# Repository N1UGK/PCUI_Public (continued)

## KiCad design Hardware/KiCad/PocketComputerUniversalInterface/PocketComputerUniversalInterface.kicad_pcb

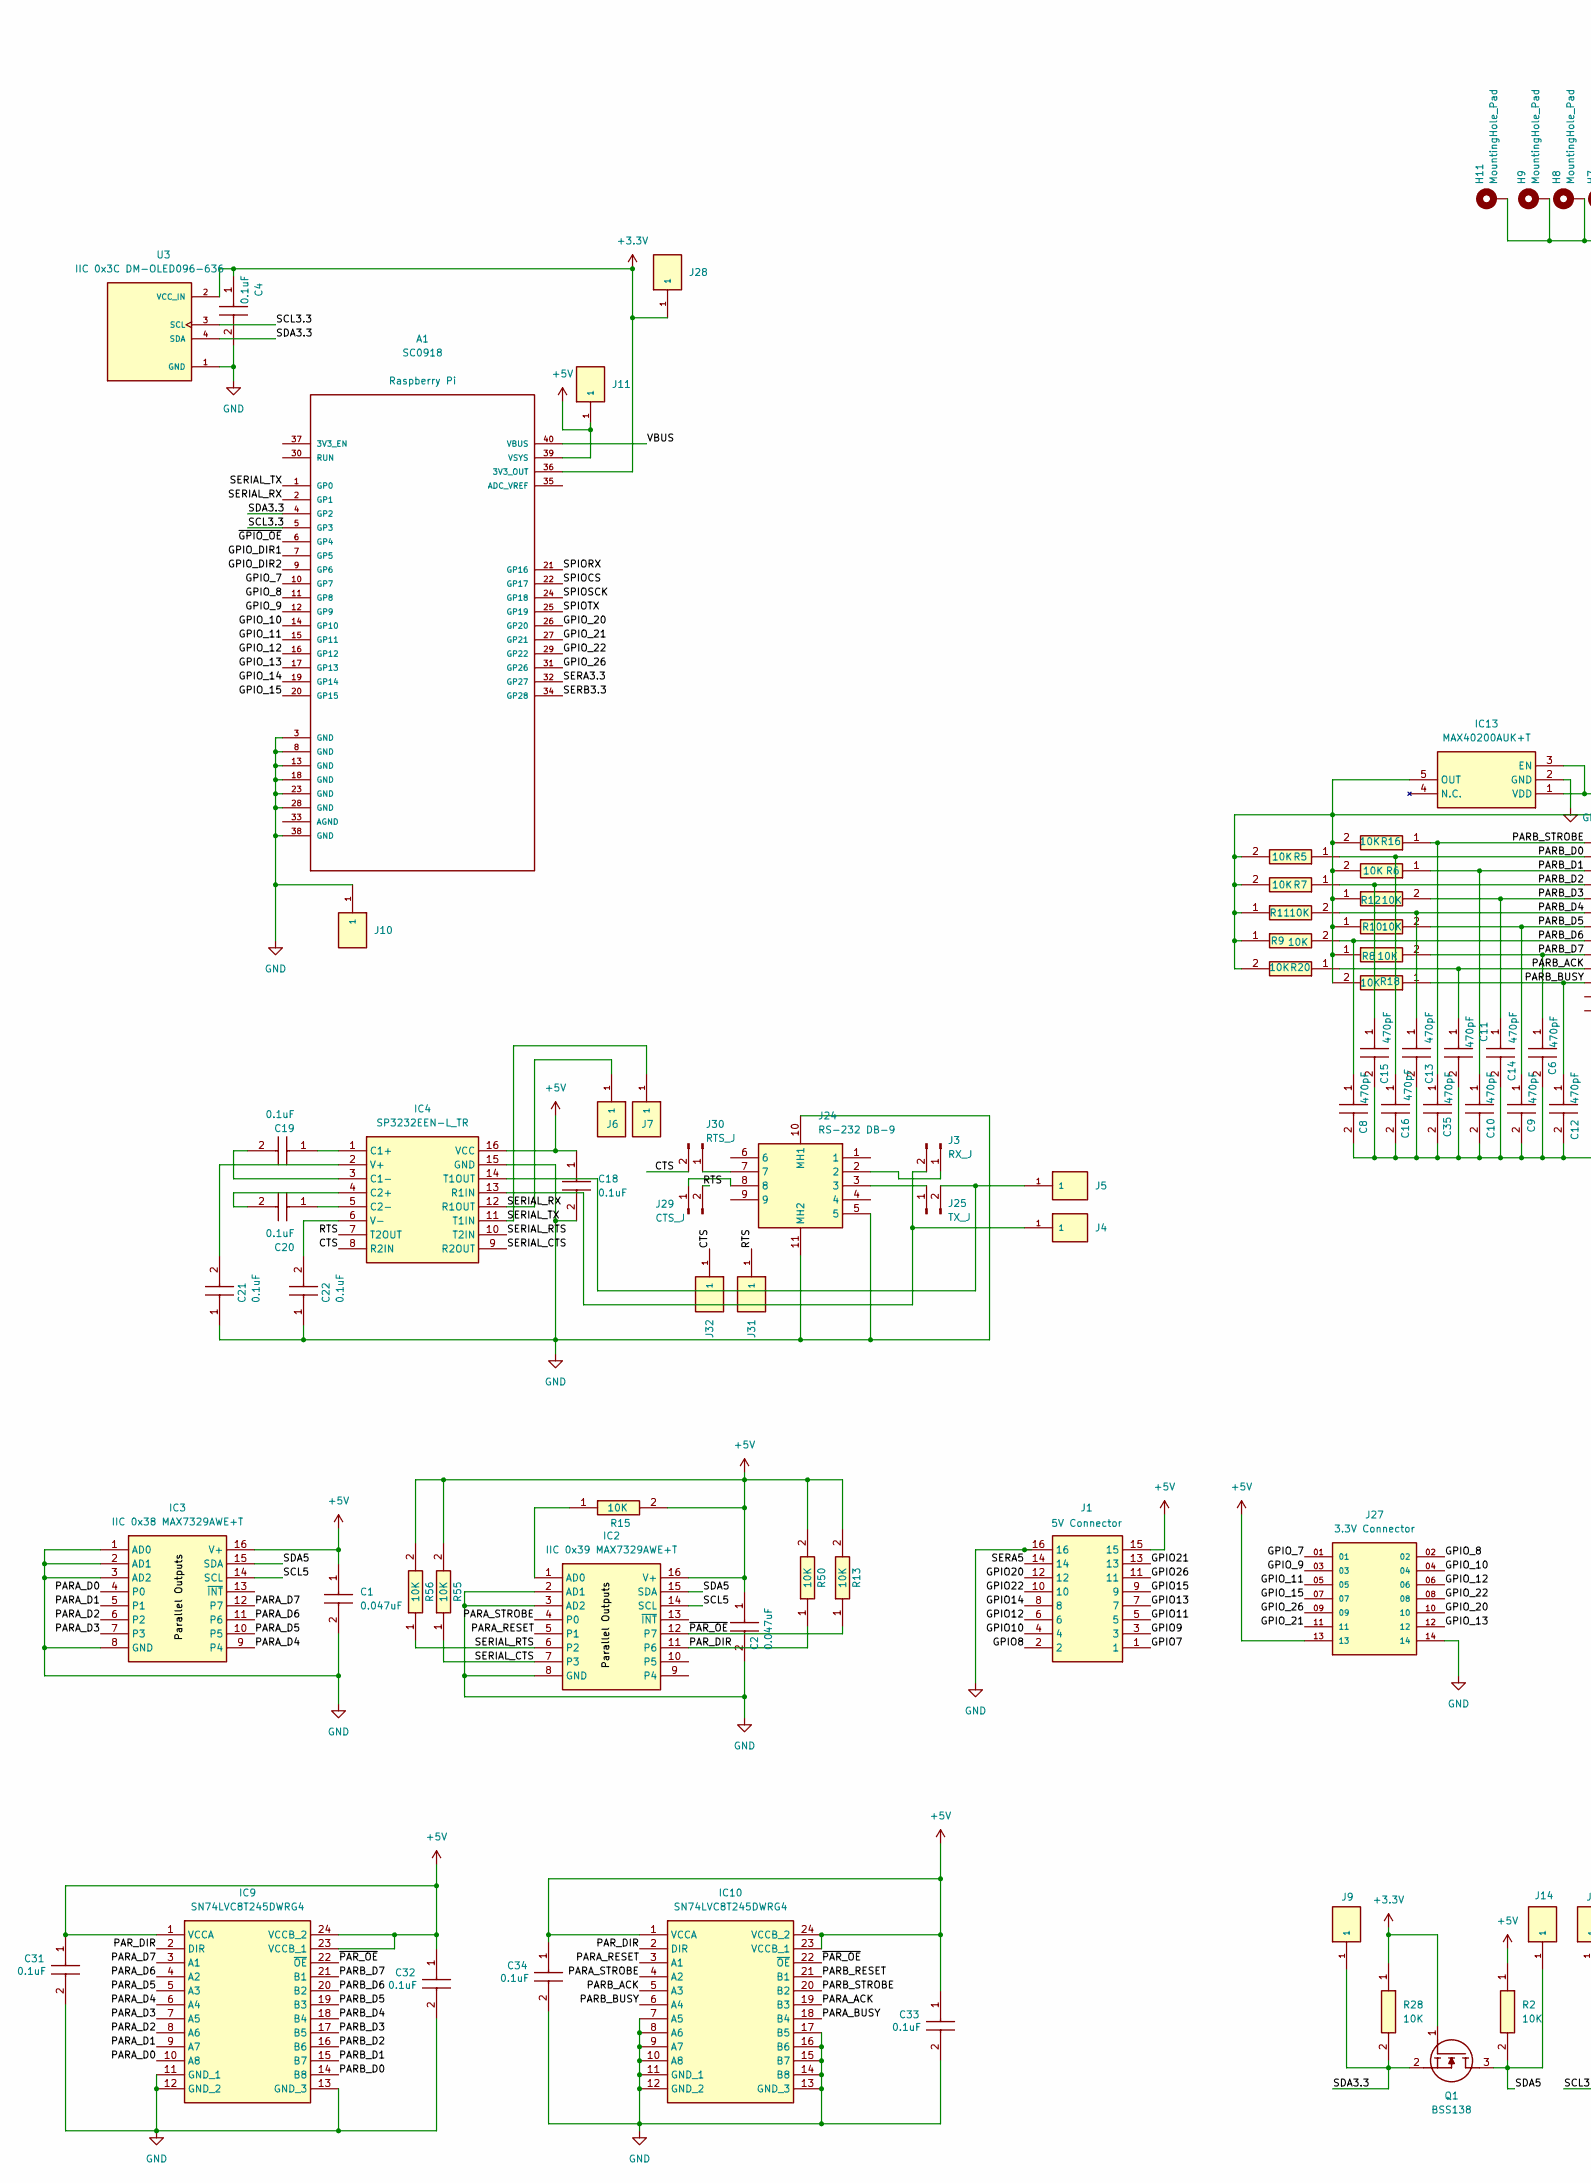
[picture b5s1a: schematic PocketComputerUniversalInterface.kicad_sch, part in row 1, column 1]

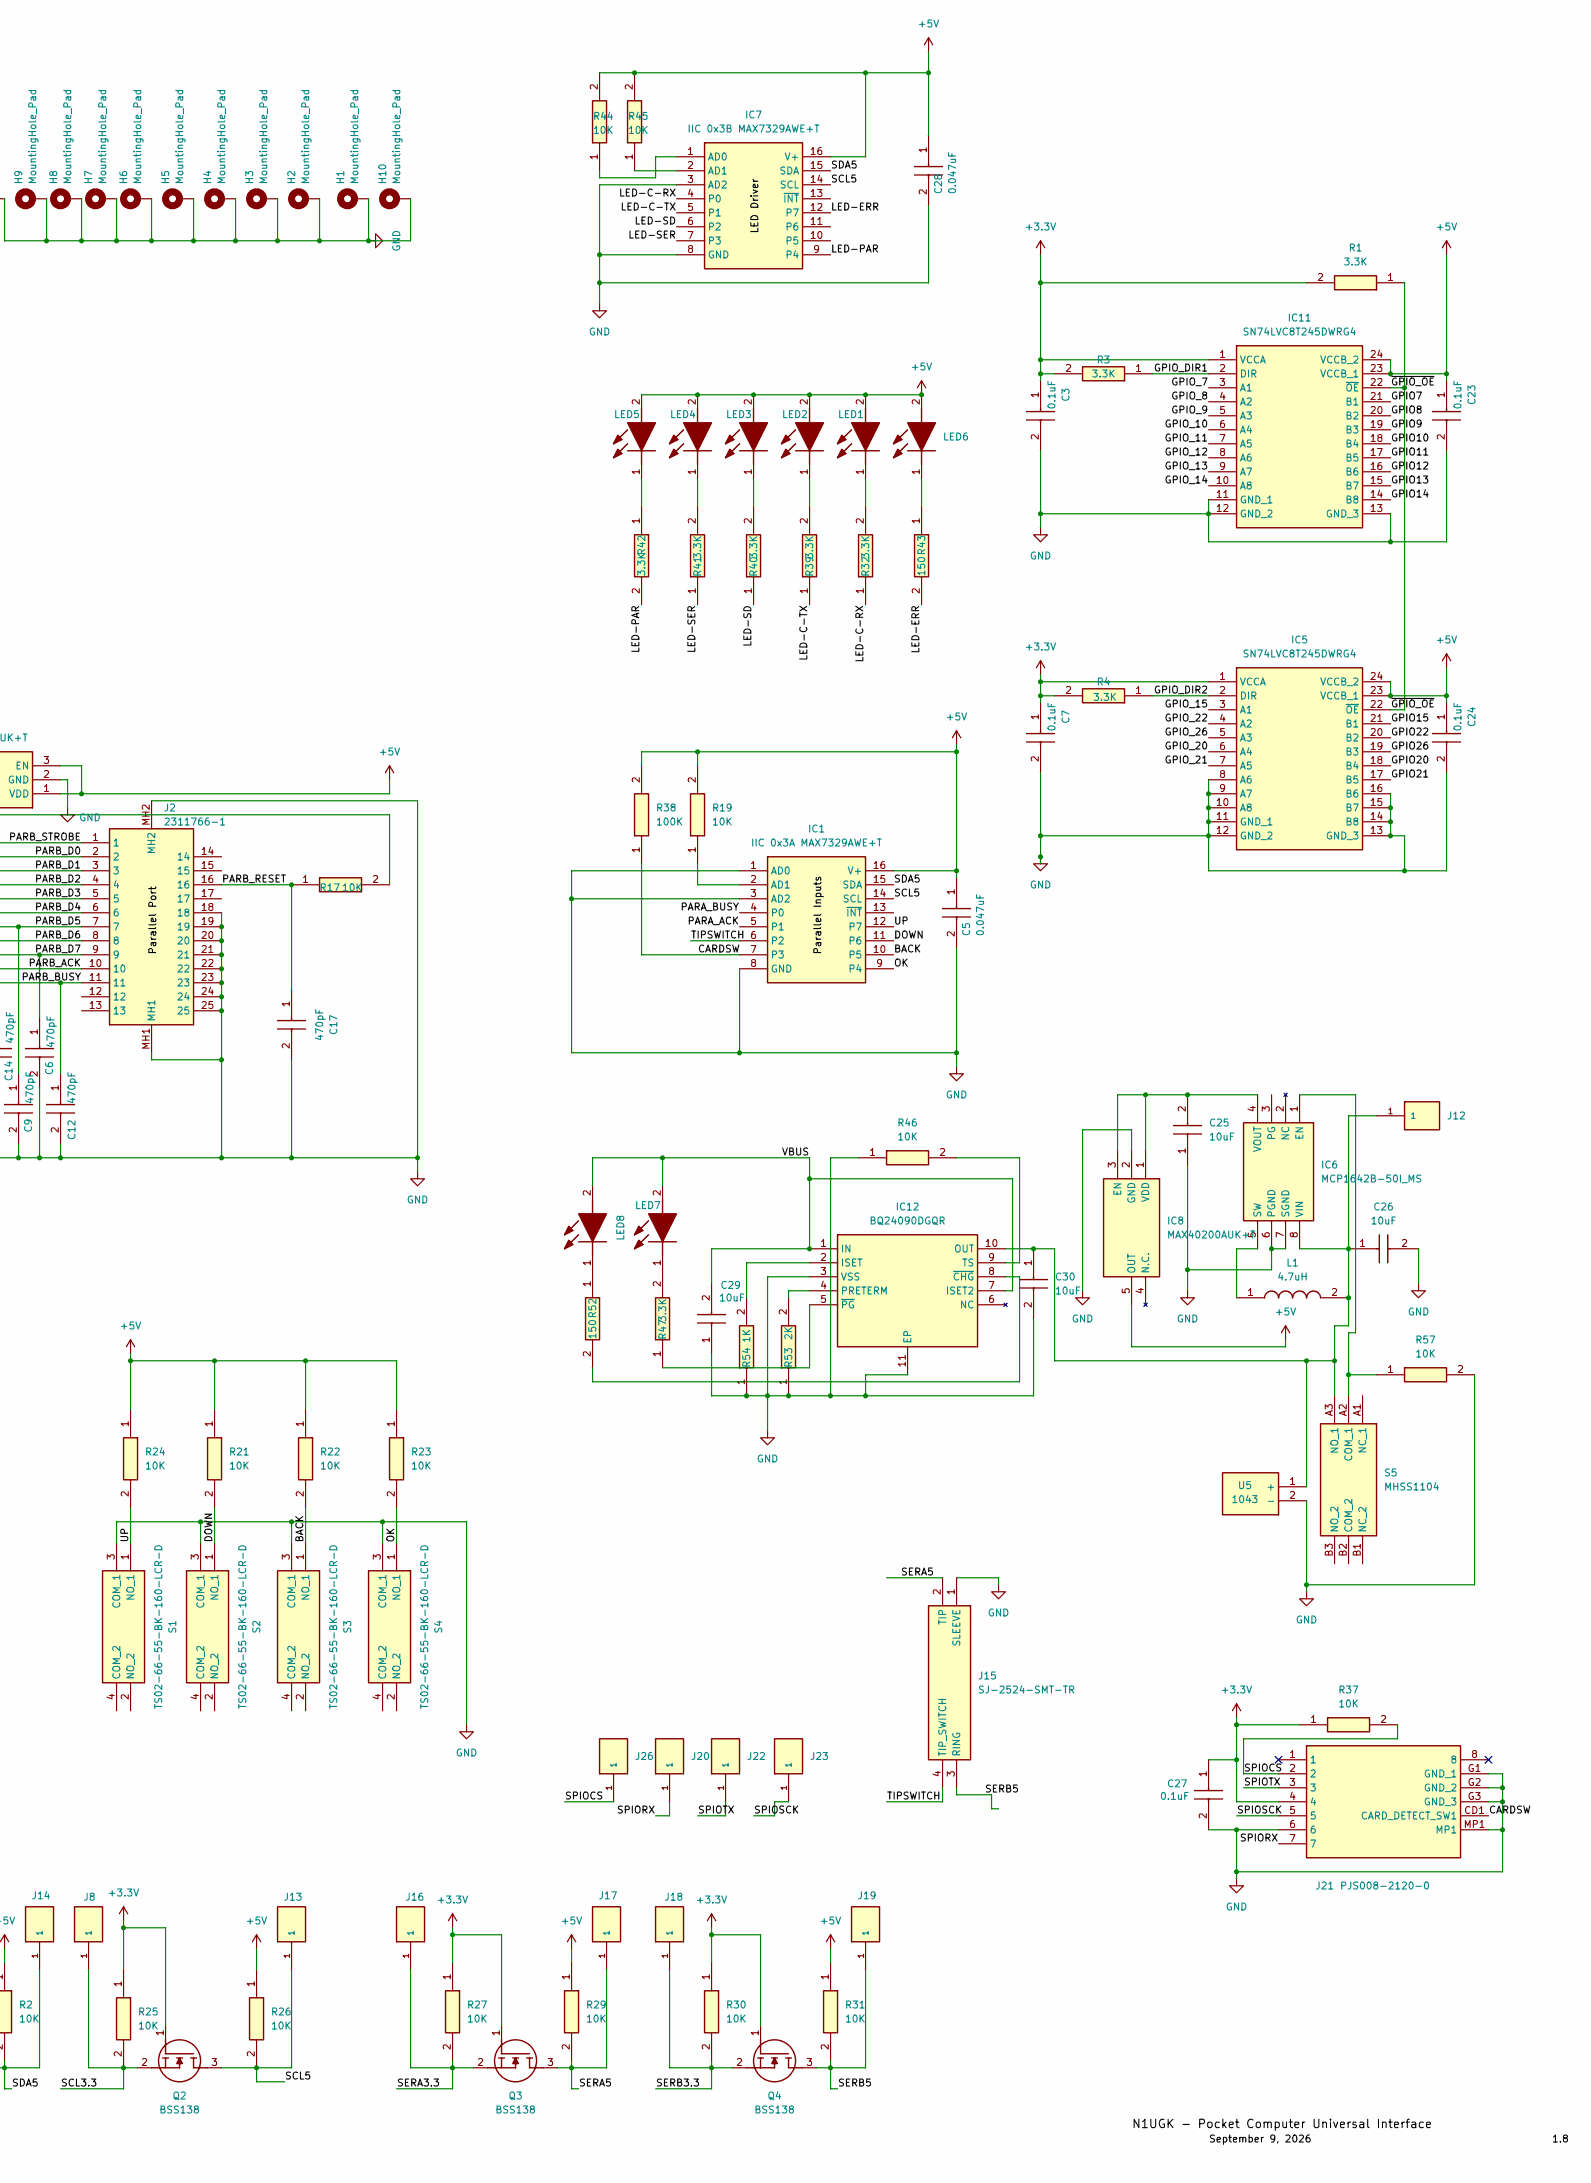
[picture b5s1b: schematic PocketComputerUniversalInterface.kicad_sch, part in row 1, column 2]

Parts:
A1: SC0918; MODULE_SC0918; PARTREV 1.6
C1, C2, C5, C28: 0.047uF; C1206; Mouser Part Number 80-C1206C473J5R
C3, C4, C7, C23, C24: 0.1uF; CAPC3216X94N; Mouser Part Number 581-12062A471KAT2A
C6, C8, C9, C10, C11, C12, C13, C14, C15, C16, C17, C35: 470pF; CAPC3216X94N; Mouser Part Number 581-12062A471KAT2A
C18, C19, C20, C21, C22, C27, C31, C32, C33, C34: 0.1uF; CAPC3216X94N; Mouser Part Number 581-12061C103J
C25, C26, C29, C30: 10uF; CAPC1608X90N; Mouser Part Number 81-GRM188R60J106ME4D
H1, H2, H3, H4, H5, H6, H7, H8, H9, H10, H11: MountingHole_Pad; MountingHole_3.2mm_M3_Pad_Via
IC1: IIC 0x3A MAX7329AWE+T; SOIC127P1032X265-16N; Mouser Part Number 700-MAX7329AWET
IC2: IIC 0x39 MAX7329AWE+T; SOIC127P1032X265-16N; Mouser Part Number 700-MAX7329AWET
IC3: IIC 0x38 MAX7329AWE+T; SOIC127P1032X265-16N; Mouser Part Number 700-MAX7329AWET
IC4: SP3232EEN-L_TR; SOIC127P600X175-16N; Mouser Part Number 701-SP3232EEN-L/TR
IC5, IC9, IC10, IC11: SN74LVC8T245DWRG4; SOIC127P1030X265-24N; Mouser Part Number 595-74LVC8T245DWRG4
IC6: MCP1642B-50I_MS; SOP65P490X110-8N; Mouser Part Number 579-MCP1642B-50I/MS
IC7: IIC 0x3B MAX7329AWE+T; SOIC127P1032X265-16N; Mouser Part Number 700-MAX7329AWET
IC8, IC13: MAX40200AUK+T; SOT95P280X145-5N; Mouser Part Number 700-MAX40200AUK+T
IC12: BQ24090DGQR; SOP50P490X110-11N; Mouser Part Number 595-BQ24090DGQR
J1: 5V Connector; TSS-108-XX-YYY-D; Manufacturer_Part_Number TSS-108-02-L-D
J2: 2311766-1; 23117661; Mouser Part Number 571-2311766-1
J3: RX_J; PinHeader_1x02_P2.54mm_Vertical
J4, J5, J6, J7, J8, J9, J10, J11, J12, J13, J14, J16, J17, J18, J19, J20, J22, J23, J26, J28, J31, J32: SAMTEC-HMTSW-101-24-X-S-290
J15: SJ-2524-SMT-TR; SJ2524SMTTR; Mouser Part Number 490-SJ-2524-SMT-TR
J21: PJS008-2120-0; PJS00821200; Mouser Part Number 945-PJS008-2120-0
J24: RS-232 DB-9; 6E17C009PBF221; Manufacturer_Part_Number 6E17C009PBF221
J25: TX_J; PinHeader_1x02_P2.54mm_Vertical
J27: 3.3V Connector; SAMTEC_TSS-107-02-H-D; PARTREV R
J29: CTS_J; PinHeader_1x02_P2.54mm_Vertical
J30: RTS_J; PinHeader_1x02_P2.54mm_Vertical
L1: 4.7uH; EPL3015472MLC; Mouser Part Number 994-EPL3015-472MLC
LED1, LED2, LED3, LED4, LED5, LED7: HSMM-A100-S00J1; LEDM3528X200N; Mouser Part Number 630-HSMM-A100-S00J1
LED6, LED8: HSMS-A100-L00J1; HSMSA100L00J1; Mouser Part Number 630-HSMS-A100-L00J1
Q1, Q2, Q3, Q4: BSS138; SOT95P240X120-3N; Mouser Part Number 512-BSS138
R1, R3, R4, R32, R39, R40, R41, R42, R47: 3.3K; RESC2013X65N; Mouser Part Number 756-WCR0805-10KFI
R2, R5, R6, R7, R8, R9, R10, R11, R12, R13, R15, R16, R17, R18, R19, R20, R21, R22, R23, R24, R25, R26, R27, R28, R29, R30, R31, R37, R44, R45, R46, R50, R55, R56, R57: 10K; RESC2013X65N; Mouser Part Number 756-WCR0805-10KFI
R38: 100K; RESC2013X65N; Mouser Part Number 756-WCR0805-10KFI
R43, R52: 150; RESC2013X65N; Mouser Part Number 756-WCR0805-10KFI
R53: 2K; RESC2013X65N; Mouser Part Number 756-WCR0805-10KFI
R54: 1K; RESC2013X65N; Mouser Part Number 756-WCR0805-10KFI
S1, S2, S3, S4: TS02-66-55-BK-160-LCR-D; TS026655BK160LCRD; Mouser Part Number 179-TS026655BK160LCR
S5: MHSS1104; Mouser Part Number 642-MHSS1104
U3: IIC 0x3C DM-OLED096-636; MODULE_DM-OLED096-636; PARTREV 2018-09-10
U5: 1043; Mouser Part Number 534-1043

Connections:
+3.3V: A1.36 (3V3_OUT), C3.1 (C1), C4.1, C7.1 (C1), C27.1 (C1), IC5.1 (VCCA), IC11.1 (VCCA), J21.4, J28.1, Q1.1 (G), Q2.1 (G), Q3.1 (G), Q4.1 (G), R1.2, R3.2, R4.2, R25.1, R27.1, R28.1, R30.1, R37.1, U3.2 (VCC_IN)
+5V: A1.39 (VSYS), C1.1, C2.1, C5.1, C18.1 (C1), C23.1 (C1), C24.1 (C1), C28.1, C31.1 (C1), C32.1 (C1), C33.1 (C1), C34.1 (C1), IC1.16 (V+), IC2.16 (V+), IC3.16 (V+), IC4.16 (VCC), IC5.23 (VCCB_1), IC5.24 (VCCB_2), IC7.16 (V+), IC8.5 (OUT), IC9.1 (VCCA), IC9.23 (VCCB_1), IC9.24 (VCCB_2), IC10.1 (VCCA), IC10.23 (VCCB_1), IC10.24 (VCCB_2), IC11.23 (VCCB_1), IC11.24 (VCCB_2), IC13.1 (VDD), IC13.3 (EN), J1.15, J11.1, J27.13, LED1.2 (A), LED2.2 (A), LED3.2 (A), LED4.2 (A), LED5.2 (A), LED6.2 (A), R2.1, R13.2, R15.2, R19.2, R21.1, R22.1, R23.1, R24.1, R26.1, R29.1, R31.1, R38.2, R44.2, R45.2, R50.2, R55.2, R56.2
/BACK: IC1.10 (P5), R22.2, S3.1 (NO_1)
/CARDSW: IC1.7 (P3), J21.CD1 (CARD_DETECT_SW1), R38.1
/CTS: IC4.8 (R2IN), J30.2, J32.1
/DOWN: IC1.11 (P6), R21.2, S2.1 (NO_1)
/GPIO7: IC11.21 (B1), J1.1
/GPIO8: IC11.20 (B2), J1.2
/GPIO9: IC11.19 (B3), J1.3
/GPIO10: IC11.18 (B4), J1.4
/GPIO11: IC11.17 (B5), J1.5
/GPIO12: IC11.16 (B6), J1.6
/GPIO13: IC11.15 (B7), J1.7
/GPIO14: IC11.14 (B8), J1.8
/GPIO15: IC5.21 (B1), J1.9
/GPIO20: IC5.18 (B4), J1.12
/GPIO21: IC5.17 (B5), J1.13
/GPIO22: IC5.20 (B2), J1.10
/GPIO26: IC5.19 (B3), J1.11
/GPIO_7: A1.10 (GP7), IC11.3 (A1), J27.01
/GPIO_8: A1.11 (GP8), IC11.4 (A2), J27.02
/GPIO_9: A1.12 (GP9), IC11.5 (A3), J27.03
/GPIO_10: A1.14 (GP10), IC11.6 (A4), J27.04
/GPIO_11: A1.15 (GP11), IC11.7 (A5), J27.05
/GPIO_12: A1.16 (GP12), IC11.8 (A6), J27.06
/GPIO_13: A1.17 (GP13), IC11.9 (A7), J27.12
/GPIO_14: A1.19 (GP14), IC11.10 (A8)
/GPIO_15: A1.20 (GP15), IC5.3 (A1), J27.07
/GPIO_20: A1.26 (GP20), IC5.6 (A4), J27.10
/GPIO_21: A1.27 (GP21), IC5.7 (A5), J27.11
/GPIO_22: A1.29 (GP22), IC5.4 (A2), J27.08
/GPIO_26: A1.31 (GP26), IC5.5 (A3), J27.09
/GPIO_DIR1: A1.7 (GP5), IC11.2 (DIR), R3.1
/GPIO_DIR2: A1.9 (GP6), IC5.2 (DIR), R4.1
/LED-C-RX: IC7.4 (P0), R32.1
/LED-C-TX: IC7.5 (P1), R39.1
/LED-ERR: IC7.12 (P7), R43.2
/LED-PAR: IC7.9 (P4), R42.2
/LED-SD: IC7.6 (P2), R40.1
/LED-SER: IC7.7 (P3), R41.1
/OK: IC1.9 (P4), R23.2, S4.1 (NO_1)
/PARA_ACK: IC1.5 (P1), IC10.19 (B3)
/PARA_BUSY: IC1.4 (P0), IC10.18 (B4)
/PARA_D0: IC3.4 (P0), IC9.10 (A8)
/PARA_D1: IC3.5 (P1), IC9.9 (A7)
/PARA_D2: IC3.6 (P2), IC9.8 (A6)
/PARA_D3: IC3.7 (P3), IC9.7 (A5)
/PARA_D4: IC3.9 (P4), IC9.6 (A4)
/PARA_D5: IC3.10 (P5), IC9.5 (A3)
/PARA_D6: IC3.11 (P6), IC9.4 (A2)
/PARA_D7: IC3.12 (P7), IC9.3 (A1)
/PARA_RESET: IC2.5 (P1), IC10.3 (A1)
/PARA_STROBE: IC2.4 (P0), IC10.4 (A2)
/PARB_ACK: C11.1 (C1), IC10.5 (A3), J2.10, R20.1
/PARB_BUSY: C12.1 (C1), IC10.6 (A4), J2.11, R18.1
/PARB_D0: C16.1 (C1), IC9.14 (B8), J2.2, R5.1
/PARB_D1: C10.1 (C1), IC9.15 (B7), J2.3, R6.1
/PARB_D2: C15.1 (C1), IC9.16 (B6), J2.4, R7.1
/PARB_D3: C14.1 (C1), IC9.17 (B5), J2.5, R12.2
/PARB_D4: C13.1 (C1), IC9.18 (B4), J2.6, R11.2
/PARB_D5: C9.1 (C1), IC9.19 (B3), J2.7, R10.2
/PARB_D6: C8.1 (C1), IC9.20 (B2), J2.8, R9.2
/PARB_D7: C6.1 (C1), IC9.21 (B1), J2.9, R8.2
/PARB_RESET: C17.1 (C1), IC10.21 (B1), J2.16, R17.1
/PARB_STROBE: C35.1 (C1), IC10.20 (B2), J2.1, R16.1
/PAR_DIR: IC2.11 (P6), IC9.2 (DIR), IC10.2 (DIR), R50.1
/RTS: IC4.7 (T2OUT), J29.2, J31.1
/SCL3.3: A1.5 (GP3), J8.1, Q2.2 (S), R25.2, U3.3 (SCL)
/SCL5: IC1.14 (SCL), IC2.14 (SCL), IC3.14 (SCL), IC7.14 (SCL), J13.1, Q2.3 (D), R26.2
/SDA3.3: A1.4 (GP2), J9.1, Q1.2 (S), R28.2, U3.4 (SDA)
/SDA5: IC1.15 (SDA), IC2.15 (SDA), IC3.15 (SDA), IC7.15 (SDA), J14.1, Q1.3 (D), R2.2
/SERA3.3: A1.32 (GP27), J16.1, Q3.2 (S), R27.2
/SERA5: J1.14, J15.2 (TIP), J17.1, Q3.3 (D), R29.2
/SERB3.3: A1.34 (GP28), J18.1, Q4.2 (S), R30.2
/SERB5: J15.3 (RING), J19.1, Q4.3 (D), R31.2
/SERIAL_CTS: IC2.7 (P3), IC4.9 (R2OUT), R55.1
/SERIAL_RTS: IC2.6 (P2), IC4.10 (T2IN), R56.1
/SERIAL_RX: A1.2 (GP1), IC4.12 (R1OUT), J6.1
/SERIAL_TX: A1.1 (GP0), IC4.11 (T1IN), J7.1
/SPIOCS: A1.22 (GP17), J21.2, J26.1, R37.2
/SPIORX: A1.21 (GP16), J20.1, J21.7
/SPIOSCK: A1.24 (GP18), J21.5, J23.1
/SPIOTX: A1.25 (GP19), J21.3, J22.1
/TIPSWITCH: IC1.6 (P2), J15.4 (TIP_SWITCH)
/UP: IC1.12 (P7), R24.2, S1.1 (NO_1)
/VBUS: A1.40 (VBUS), C29.2, IC12.1 (IN), IC12.7 (ISET2), LED7.2 (A), LED8.2 (A)
/~GPIO_OE: A1.6 (GP4), IC5.22 (~OE), IC11.22 (~OE), R1.1
/~PAR_OE: IC2.12 (P7), IC9.22 (~OE), IC10.22 (~OE), R13.1
GND: A1.3 (GND), A1.8 (GND), A1.13 (GND), A1.18 (GND), A1.23 (GND), A1.28 (GND), A1.38 (GND), C1.2, C2.2, C3.2 (C2), C4.2, C5.2, C6.2 (C2), C7.2 (C2), C8.2 (C2), C9.2 (C2), C10.2 (C2), C11.2 (C2), C12.2 (C2), C13.2 (C2), C14.2 (C2), C15.2 (C2), C16.2 (C2), C17.2 (C2), C18.2 (C2), C21.1 (C1), C22.1 (C1), C23.2 (C2), C24.2 (C2), C25.1, C26.2, C27.2 (C2), C28.2, C29.1, C30.2, C31.2 (C2), C32.2 (C2), C33.2 (C2), C34.2 (C2), C35.2 (C2), H1.1, H2.1, H3.1, H4.1, H5.1, H6.1, H7.1, H8.1, H9.1, H10.1, H11.1, IC1.1 (AD0), IC1.3 (AD2), IC1.8 (GND), IC2.2 (AD1), IC2.3 (AD2), IC2.8 (GND), IC3.1 (AD0), IC3.2 (AD1), IC3.3 (AD2), IC3.8 (GND), IC4.15 (GND), IC5.8 (A6), IC5.9 (A7), IC5.10 (A8), IC5.11 (GND_1), IC5.12 (GND_2), IC5.13 (GND_3), IC5.14 (B8), IC5.15 (B7), IC5.16 (B6), IC6.6 (PGND), IC6.7 (SGND), IC7.3 (AD2), IC7.8 (GND), IC8.2 (GND), IC9.11 (GND_1), IC9.12 (GND_2), IC9.13 (GND_3), IC10.7 (A5), IC10.8 (A6), IC10.9 (A7), IC10.10 (A8), IC10.11 (GND_1), IC10.12 (GND_2), IC10.13 (GND_3), IC10.14 (B8), IC10.15 (B7), IC10.16 (B6), IC10.17 (B5), IC11.11 (GND_1), IC11.12 (GND_2), IC11.13 (GND_3), IC12.3 (VSS), IC12.11 (EP), IC13.2 (GND), J1.16, J2.18, J2.19, J2.20, J2.21, J2.22, J2.23, J2.24, J2.25, J2.MH1, J2.MH2, J10.1, J15.1 (SLEEVE), J21.6, J21.G1 (GND_1), J21.G2 (GND_2), J21.G3 (GND_3), J21.MP1, J24.5, J24.10 (MH1), J24.11 (MH2), J27.14, R46.1, R53.1, R54.1, R57.2, S1.3 (COM_1), S2.3 (COM_1), S3.3 (COM_1), S4.3 (COM_1), U3.1 (GND), U5.2 (-)
unnamed: C19.1 (C1), IC4.1 (C1+)
unnamed: C19.2 (C2), IC4.3 (C1-)
unnamed: C20.1 (C1), IC4.5 (C2-)
unnamed: C20.2 (C2), IC4.4 (C2+)
unnamed: C21.2 (C2), IC4.2 (V+)
unnamed: C22.2 (C2), IC4.6 (V-)
unnamed: IC1.2 (AD1), R19.1
unnamed: IC2.1 (AD0), R15.1
unnamed: IC4.13 (R1IN), J3.2, J4.1
unnamed: IC4.14 (T1OUT), J5.1, J25.2
unnamed: IC6.1 (EN), R57.1, S5.A2 (COM_1)
unnamed: IC6.5 (SW), L1.1
unnamed: C25.2, IC6.4 (VOUT), IC8.1 (VDD), IC8.3 (EN)
unnamed: IC7.1 (AD0), R44.1
unnamed: IC7.2 (AD1), R45.1
unnamed: IC12.2 (ISET), R54.2
unnamed: C26.1, C30.1, IC6.8 (VIN), IC12.10 (OUT), J12.1, L1.2, S5.A3 (NO_1), U5.1 (+)
unnamed: IC12.4 (PRETERM), R53.2
unnamed: IC12.9 (TS), R46.2
unnamed: IC12.8 (~CHG), R52.2
unnamed: IC12.5 (~PG), R47.1
unnamed: IC13.5 (OUT), R5.2, R6.2, R7.2, R8.1, R9.1, R10.1, R11.1, R12.1, R16.2, R17.2, R18.2, R20.2
unnamed: J3.1, J24.2
unnamed: J24.3, J25.1
unnamed: J24.8, J29.1
unnamed: J24.7, J30.1
unnamed: LED1.1 (K), R32.2
unnamed: LED2.1 (K), R39.2
unnamed: LED3.1 (K), R40.2
unnamed: LED4.1 (K), R41.2
unnamed: LED5.1 (K), R42.1
unnamed: LED6.1 (K), R43.1
unnamed: LED7.1 (K), R47.2
unnamed: LED8.1 (K), R52.1

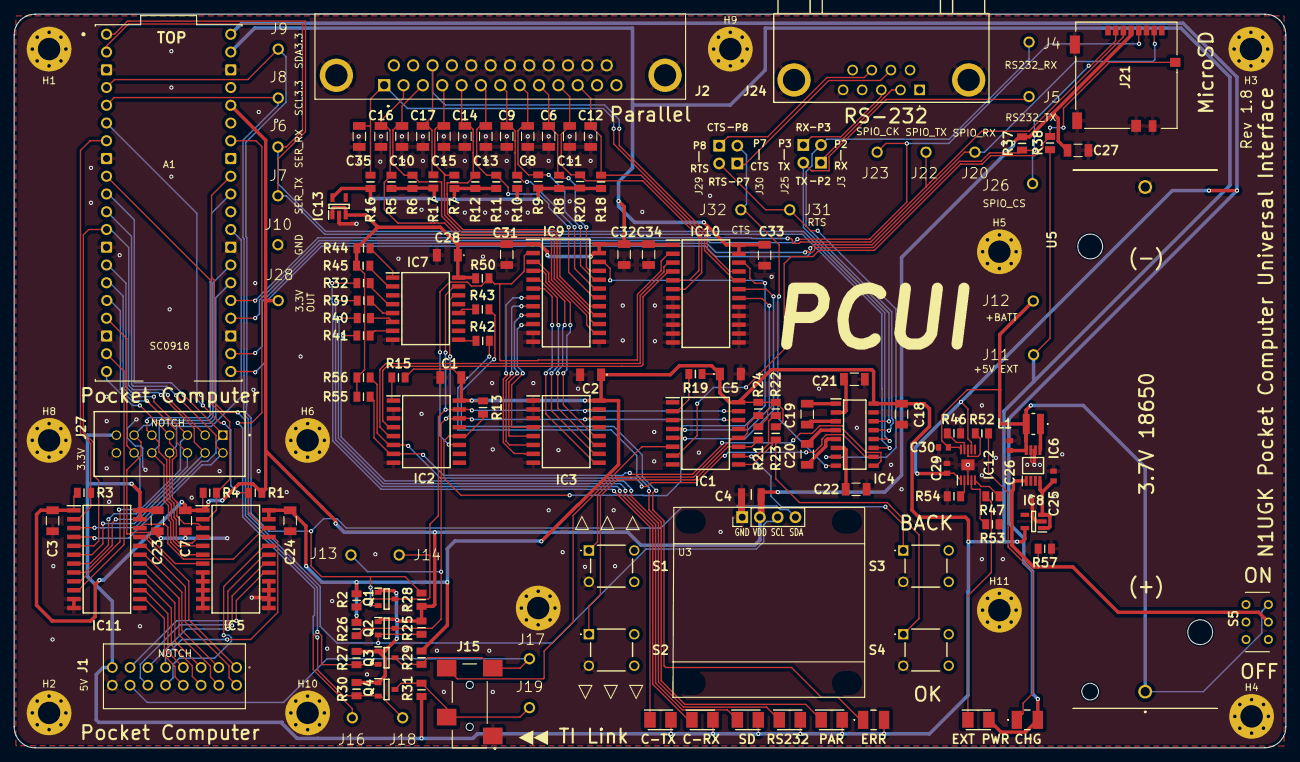
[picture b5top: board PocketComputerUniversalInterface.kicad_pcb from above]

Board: 2 copper layers, 182.0 x 105.0 mm, 161 parts (0 on the bottom side), 123 nets.

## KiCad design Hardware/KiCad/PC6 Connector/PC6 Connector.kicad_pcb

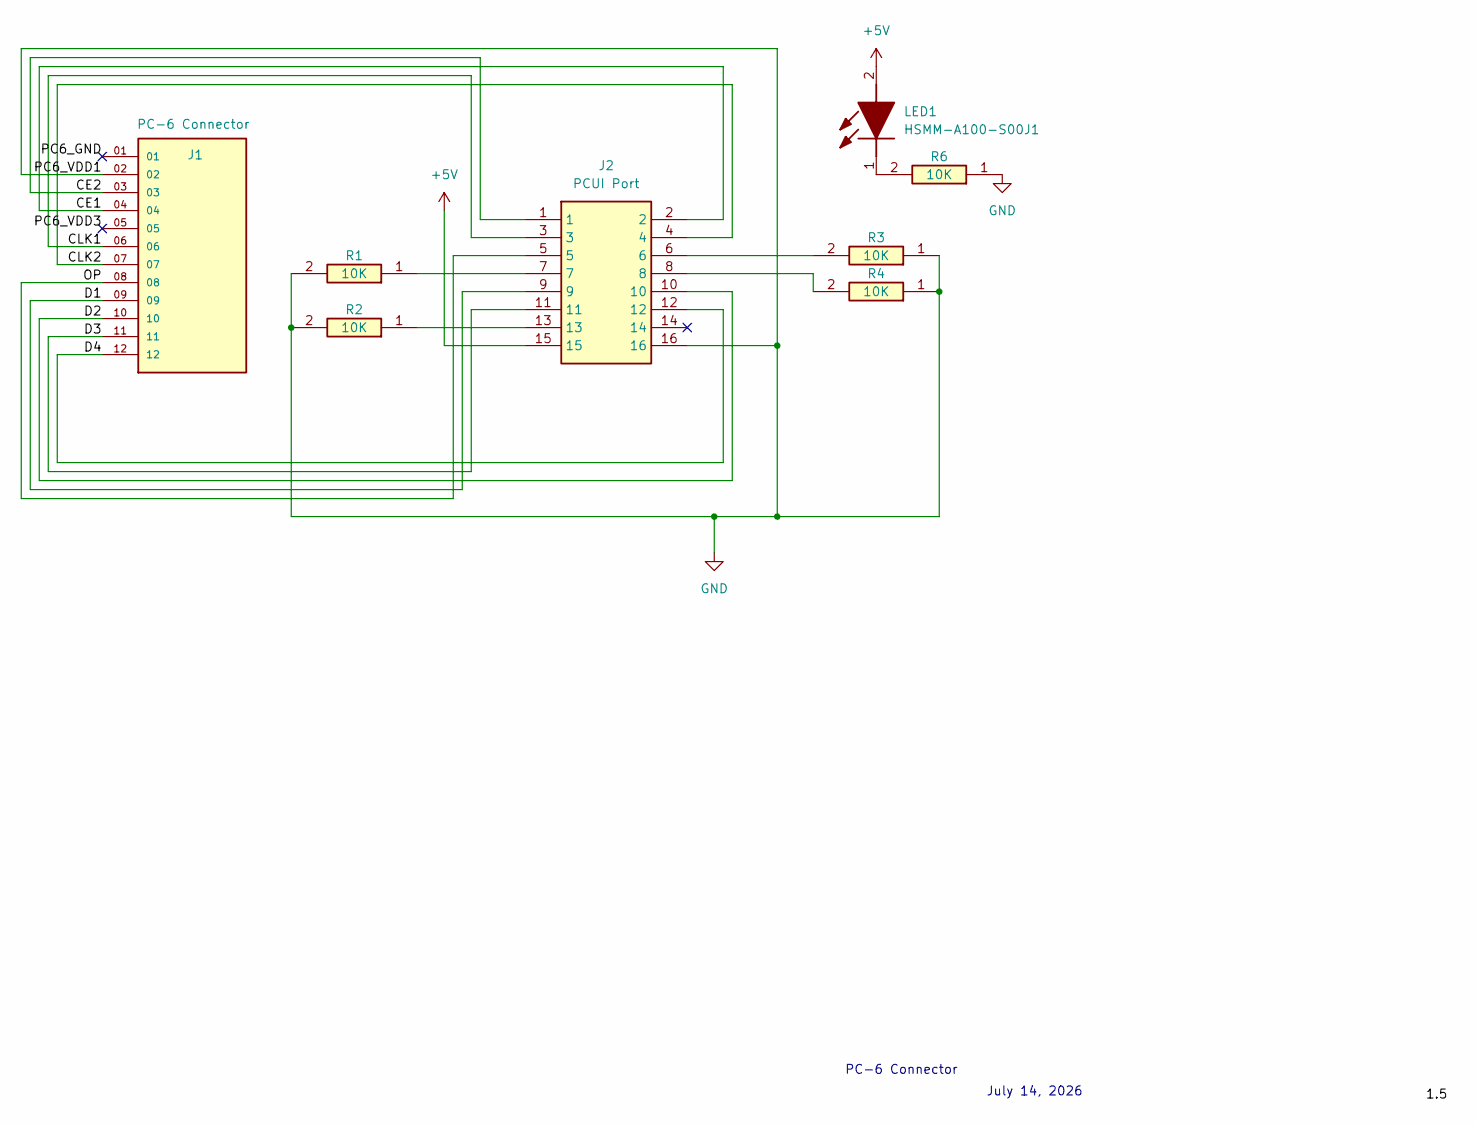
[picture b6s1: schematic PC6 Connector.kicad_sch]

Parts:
J1: PC-6 Connector; SAMTEC_TSW-112-07-L-S-LL; PARTREV R
J2: PCUI Port; TSS-108-XX-YYY-D; Manufacturer_Part_Number TSS-108-02-L-D
LED1: HSMM-A100-S00J1; LEDM3528X200N; Mouser Part Number 630-HSMM-A100-S00J1
R1, R2, R3, R4, R6: 10K; RESC2013X65N; Mouser Part Number 756-WCR0805-10KFI

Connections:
+5V: J2.15, LED1.2 (A)
/CE1: J1.04, J2.2
/CE2: J1.03, J2.1
/CLK1: J1.06, J2.3
/CLK2: J1.07, J2.4
/D1: J1.09, J2.9
/D2: J1.10, J2.10
/D3: J1.11, J2.11
/D4: J1.12, J2.12
/OP: J1.08, J2.5
/PC6_GND: J1.01
/PC6_VDD3: J1.05
GND: J1.02, J2.16, R1.2, R2.2, R3.1, R4.1, R6.1
unnamed: J2.6, R3.2
unnamed: J2.7, R1.1
unnamed: J2.8, R4.2
unnamed: J2.13, R2.1
unnamed: LED1.1 (K), R6.2

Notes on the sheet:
July 14, 2026
PC-6 Connector

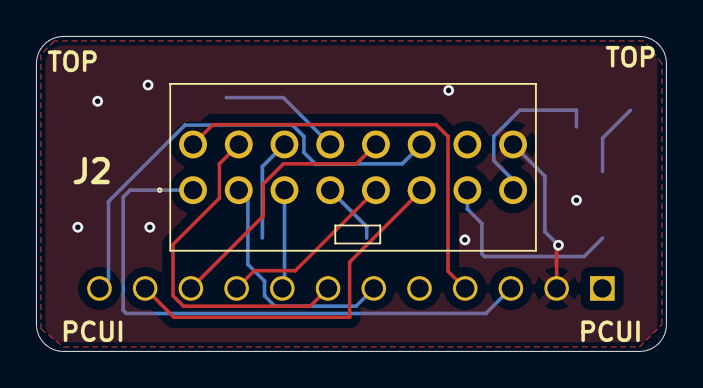
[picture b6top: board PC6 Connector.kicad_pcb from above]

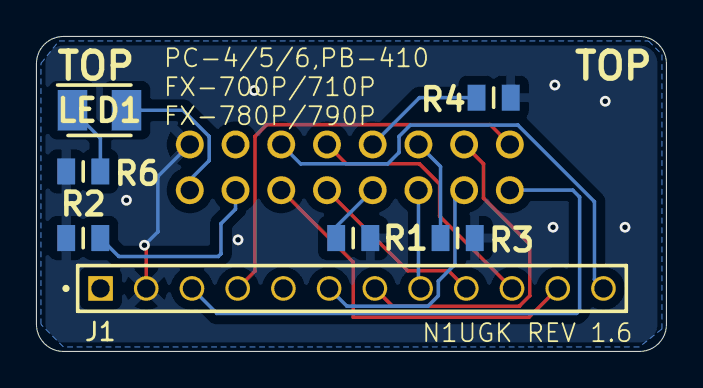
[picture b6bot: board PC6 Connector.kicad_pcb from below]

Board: 2 copper layers, 35.0 x 17.5 mm, 8 parts (7 on the bottom side), 16 nets.

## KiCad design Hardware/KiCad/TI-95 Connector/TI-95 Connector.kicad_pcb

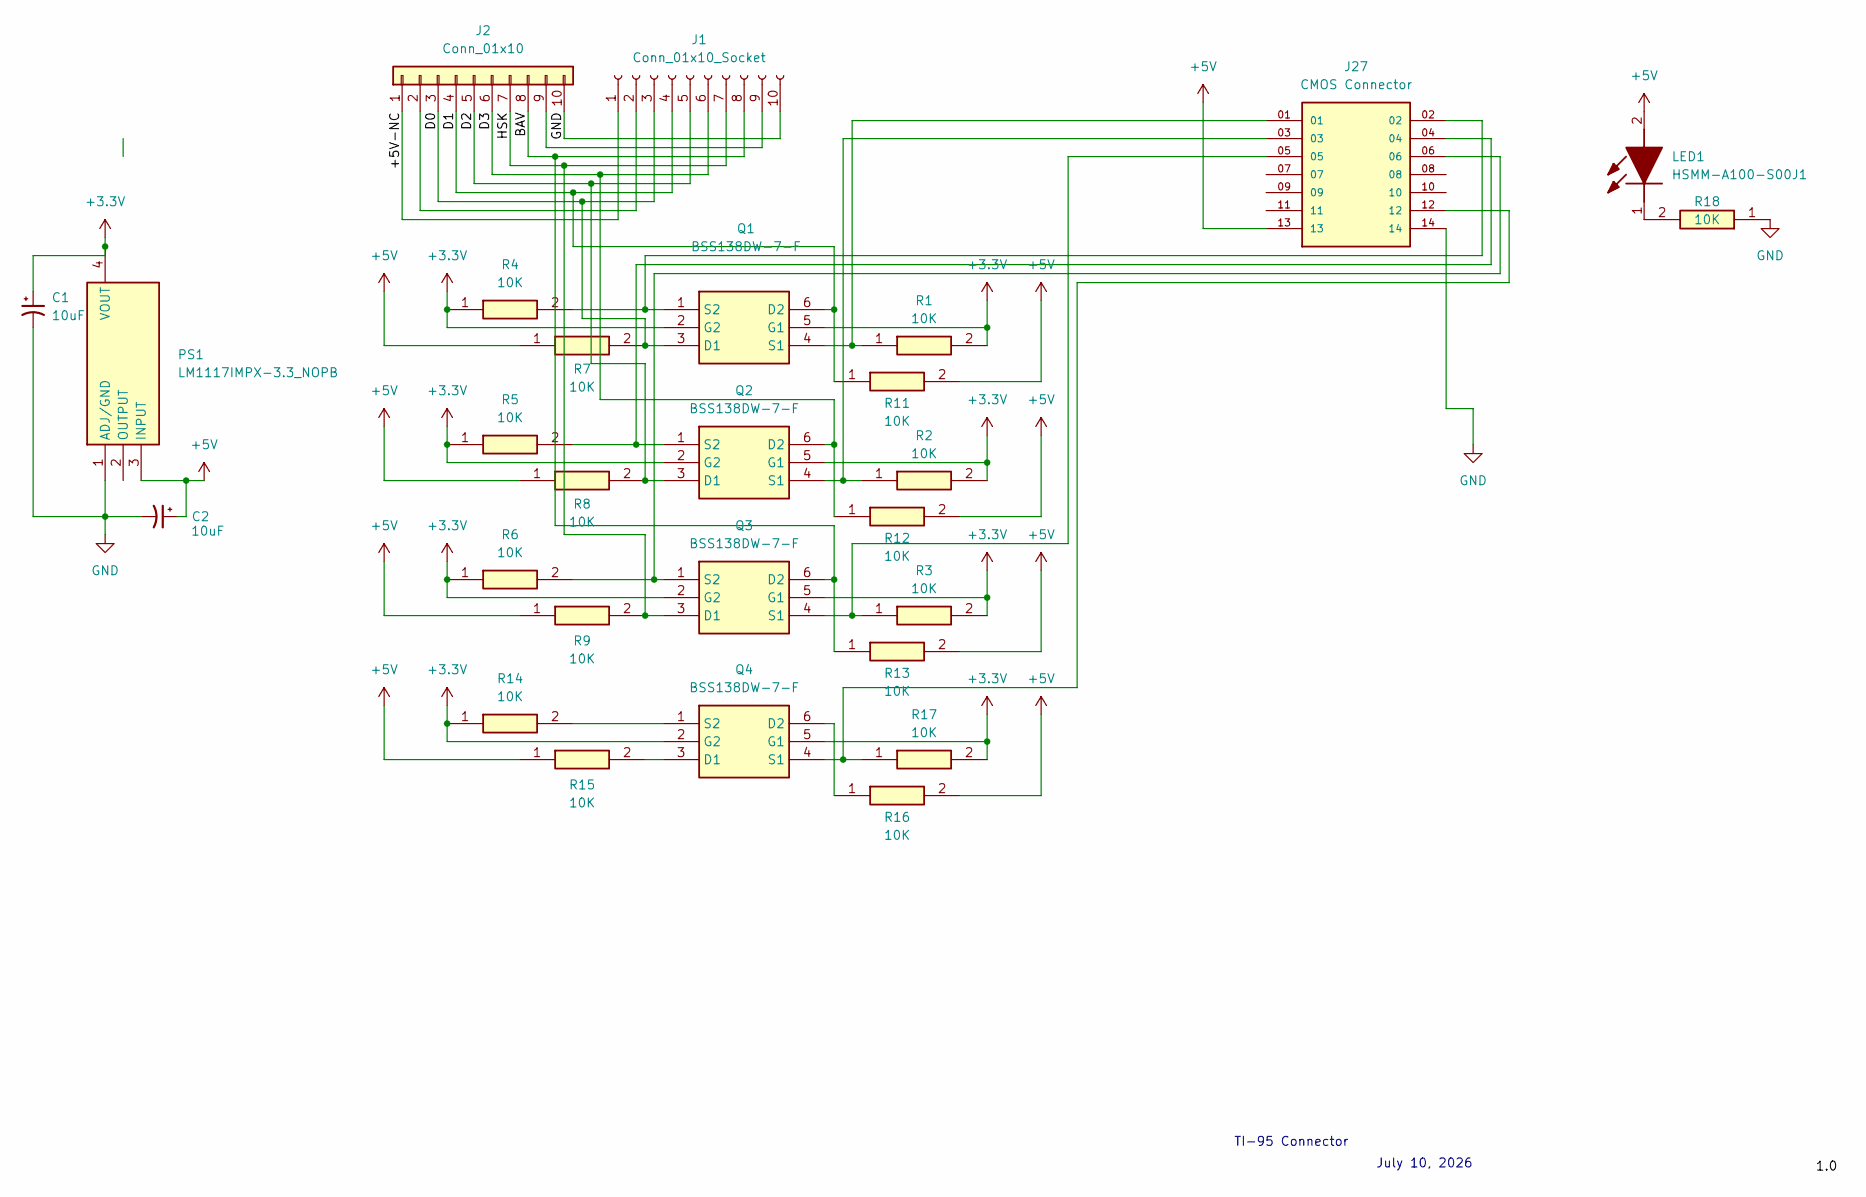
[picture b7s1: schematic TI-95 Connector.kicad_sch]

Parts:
C1, C2: 10uF; CP_EIA-3528-15_AVX-H_HandSolder
J1: Conn_01x10_Socket; PinSocket_1x10_P2.54mm_Vertical
J2: Conn_01x10; PinHeader_1x10_P2.54mm_Vertical
J27: CMOS Connector; SAMTEC_TSS-107-02-H-D; PARTREV R
LED1: HSMM-A100-S00J1; LEDM3528X200N; Mouser Part Number 630-HSMM-A100-S00J1
PS1: LM1117IMPX-3.3_NOPB; SOT230P700X180-4N; Mouser Part Number 926-LM1117IMPX33NOPB
Q1, Q2, Q3, Q4: BSS138DW-7-F; SOT65P210X110-6N; Mouser Part Number 621-BSS138DW-F
R1, R2, R3, R4, R5, R6, R7, R8, R9, R11, R12, R13, R14, R15, R16, R17, R18: 10K; RESC2013X65N; Mouser Part Number 756-WCR0805-10KFI

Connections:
+3.3V: C1.1, PS1.4 (VOUT), Q1.2 (G2), Q1.5 (G1), Q2.2 (G2), Q2.5 (G1), Q3.2 (G2), Q3.5 (G1), Q4.2 (G2), Q4.5 (G1), R1.2, R2.2, R3.2, R4.1, R5.1, R6.1, R14.1, R17.2
+5V: C2.1, J27.13, LED1.2 (A), PS1.3 (INPUT), R7.1, R8.1, R9.1, R11.2, R12.2, R13.2, R15.1, R16.2
/+5V-NC: J1.1, J2.1
/BAV: J1.8, J2.8, Q3.6 (D2), R13.1
/D0: J1.3, J2.3, Q1.3 (D1), R7.2
/D1: J1.4, J2.4, Q1.6 (D2), R11.1
/D2: J1.5, J2.5, Q2.3 (D1), R8.2
/D3: J1.6, J2.6, Q2.6 (D2), R12.1
/HSK: J1.7, J2.7, Q3.3 (D1), R9.2
GND: C1.2, C2.2, J1.10, J2.10, J27.14, PS1.1 (ADJ/GND), R18.1
unnamed: J1.2, J2.2
unnamed: J1.9, J2.9
unnamed: LED1.1 (K), R18.2
unnamed: J27.01, Q1.4 (S1), R1.1
unnamed: J27.02, Q1.1 (S2), R4.2
unnamed: J27.03, Q2.4 (S1), R2.1
unnamed: J27.04, Q2.1 (S2), R5.2
unnamed: J27.05, Q3.4 (S1), R3.1
unnamed: J27.06, Q3.1 (S2), R6.2
unnamed: Q4.3 (D1), R15.2
unnamed: Q4.6 (D2), R16.1
unnamed: J27.12, Q4.4 (S1), R17.1
unnamed: Q4.1 (S2), R14.2

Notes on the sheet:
July 10, 2026
TI-95 Connector

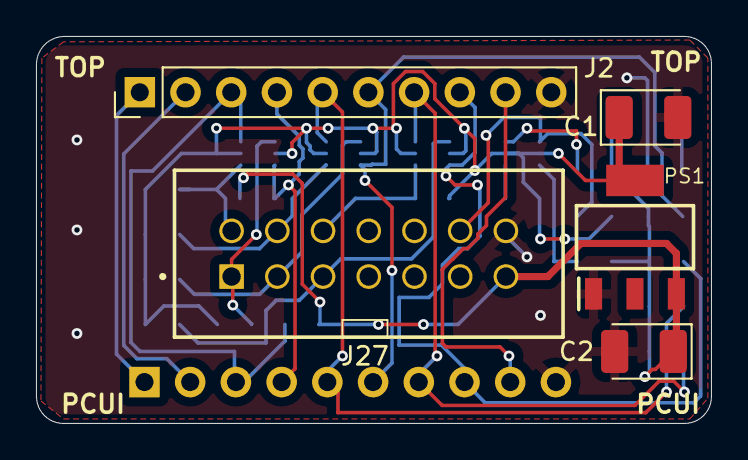
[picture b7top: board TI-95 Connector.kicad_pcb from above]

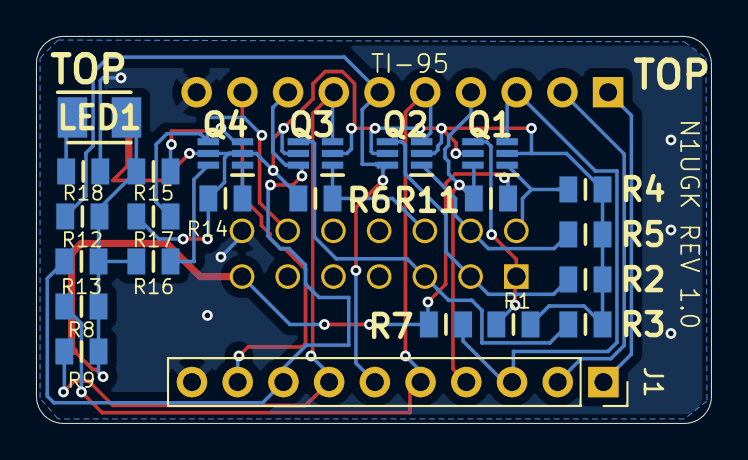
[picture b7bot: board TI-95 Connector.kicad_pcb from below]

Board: 2 copper layers, 37.5 x 21.5 mm, 28 parts (23 on the bottom side), 23 nets.

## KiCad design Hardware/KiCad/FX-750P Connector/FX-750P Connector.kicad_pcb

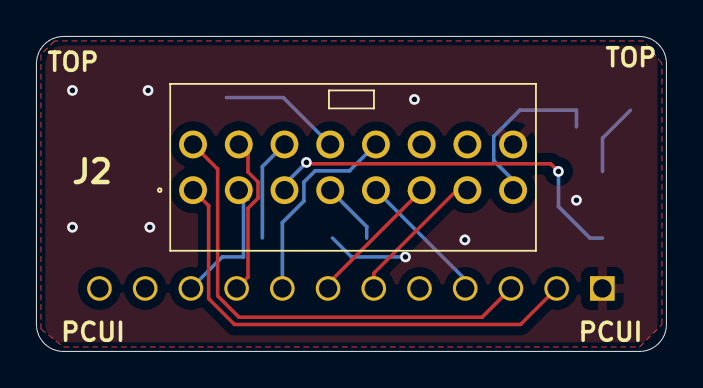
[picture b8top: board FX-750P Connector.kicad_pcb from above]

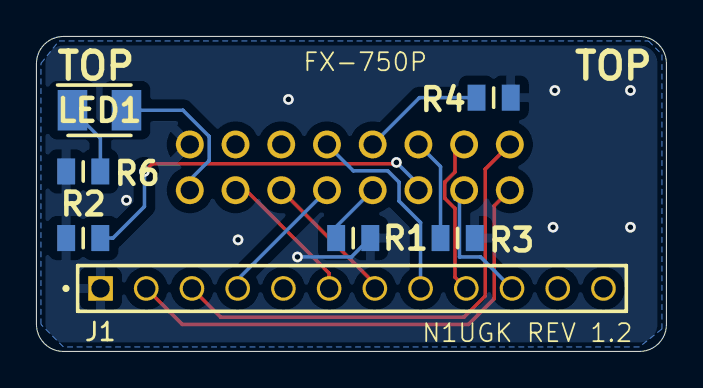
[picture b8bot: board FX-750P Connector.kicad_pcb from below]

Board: 2 copper layers, 35.0 x 17.5 mm, 8 parts (7 on the bottom side), 15 nets.

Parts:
J1: FX-750P Connector; SAMTEC_TSW-112-07-L-S-LL
J2: PCUI Port; TSS-108-XX-YYY-D
LED1: HSMM-A100-S00J1; LEDM3528X200N
R1, R2, R3, R4, R6: 10K; RESC2013X65N

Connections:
+5V: J2.15, LED1.2 (A)
/CE1: J1.03, J2.2
/CE2: J1.02, J2.1
/CK1: J1.10, J2.3
/CK2: J1.09, J2.4
/D1: J1.04, J2.9
/D2: J1.08, J2.10
/D3: J1.07, J2.11
/GPIO11: J2.5, R2.1
/GPIO12: J2.6, R3.2
/GPIO13: J2.7, R1.1
/GPIO14: J2.8, R4.2
/GPIO21: J1.06, J2.13
GND: J1.01, J2.16, R1.2, R2.2, R3.1, R4.1, R6.1
unnamed: LED1.1 (K), R6.2

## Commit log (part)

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2026-05-11 Added first public firmware release and 2 sample programs for the 1401 series.
2026-05-11 Revise README with new title and project details
    Updated project title and added description with image.
2026-05-11 Fix capitalization in project title
    Corrected the capitalization in the project title.
2026-05-21 Added sample programs
2026-05-26 Updated programs and added documentation
2026-06-14 Updated documentation for self-test mode.
2026-06-19 Added owners manuals, organized banner program.
2026-06-20 Remove owners manual link from README
    Removed the link to the PCUI Owners Manual from the README.
2026-06-22 Enhance README with cassette interface information
    Added details about true low-level cassette interface integration.
2026-06-27 Updated documentation
2026-06-28 Organized PB-700 Programs
